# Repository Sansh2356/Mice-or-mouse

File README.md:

# Mouse PCB

Reverse-engineering the PCB of an optical mouse by tearing down wired single-chip and wireless dual-chip mice.
The circuit is traced using continuity measurements, then recreated in KiCad as a schematic, custom symbols/footprints, and a PCB layout.
Gerber files for the V1 board are generated and included in `gerbers/`.

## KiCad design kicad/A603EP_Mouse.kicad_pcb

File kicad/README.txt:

A603EP Mouse Clone - KiCad project
==================================
KiCad 7 format; opens in KiCad 7, 8 and 9 (newer versions offer to upgrade - click Yes).

Files
- A603EP_Mouse.kicad_pro        Project - open this
- A603EP_Mouse.kicad_sch        Schematic traced from board HYC-343-1
- A603EP_Mouse.kicad_pcb        PCB: outline, wheel slot, cable notch, chip/LED window, 8 holes,
                                and every part placed at its original position (not yet routed)
- A603EP_Mouse.kicad_sym / .pretty   Project symbols and footprints
- A603EP_PCB_fit_test.pdf       1:1 print to check the board against the original and the shell
- A603EP_Mouse_schematic.pdf    Printable schematic

How it was made
- Chip footprint: 1.778 mm pitch, 14.0 mm row spacing (confirmed by your paper test, option B).
- Everything else measured from your straight-down photo of the green side, using the chip pads
  as the ruler. Board comes out 38.9 x 66.4 mm (your ruler: 40 x 65). Accuracy about +-0.3 mm.
- KiCad's netlist and the PCB pad nets match the schematic exactly.

CHECKS - ALL DONE (19 Oct 2026)
- 1:1 fit test passed on the original board and in the shell.
- Encoder common = front outer leg; + = left leg for LED1, C1, D1-D4 ('+' marked on silkscreen); SW6 has 2 legs.
- Micro-switches: middle leg = common (pin 1), front = normally-open (pin 2), back = normally-closed (unused).

THEN ROUTE
- Route on one side (B.Cu) like the original if you want to etch at home, or use both sides
  if a fab makes it. Keep C2 close to U1 pins 10/11 and the USB tracks short.
- Run Inspect > Design Rules Checker. Order 1.6 mm thickness.

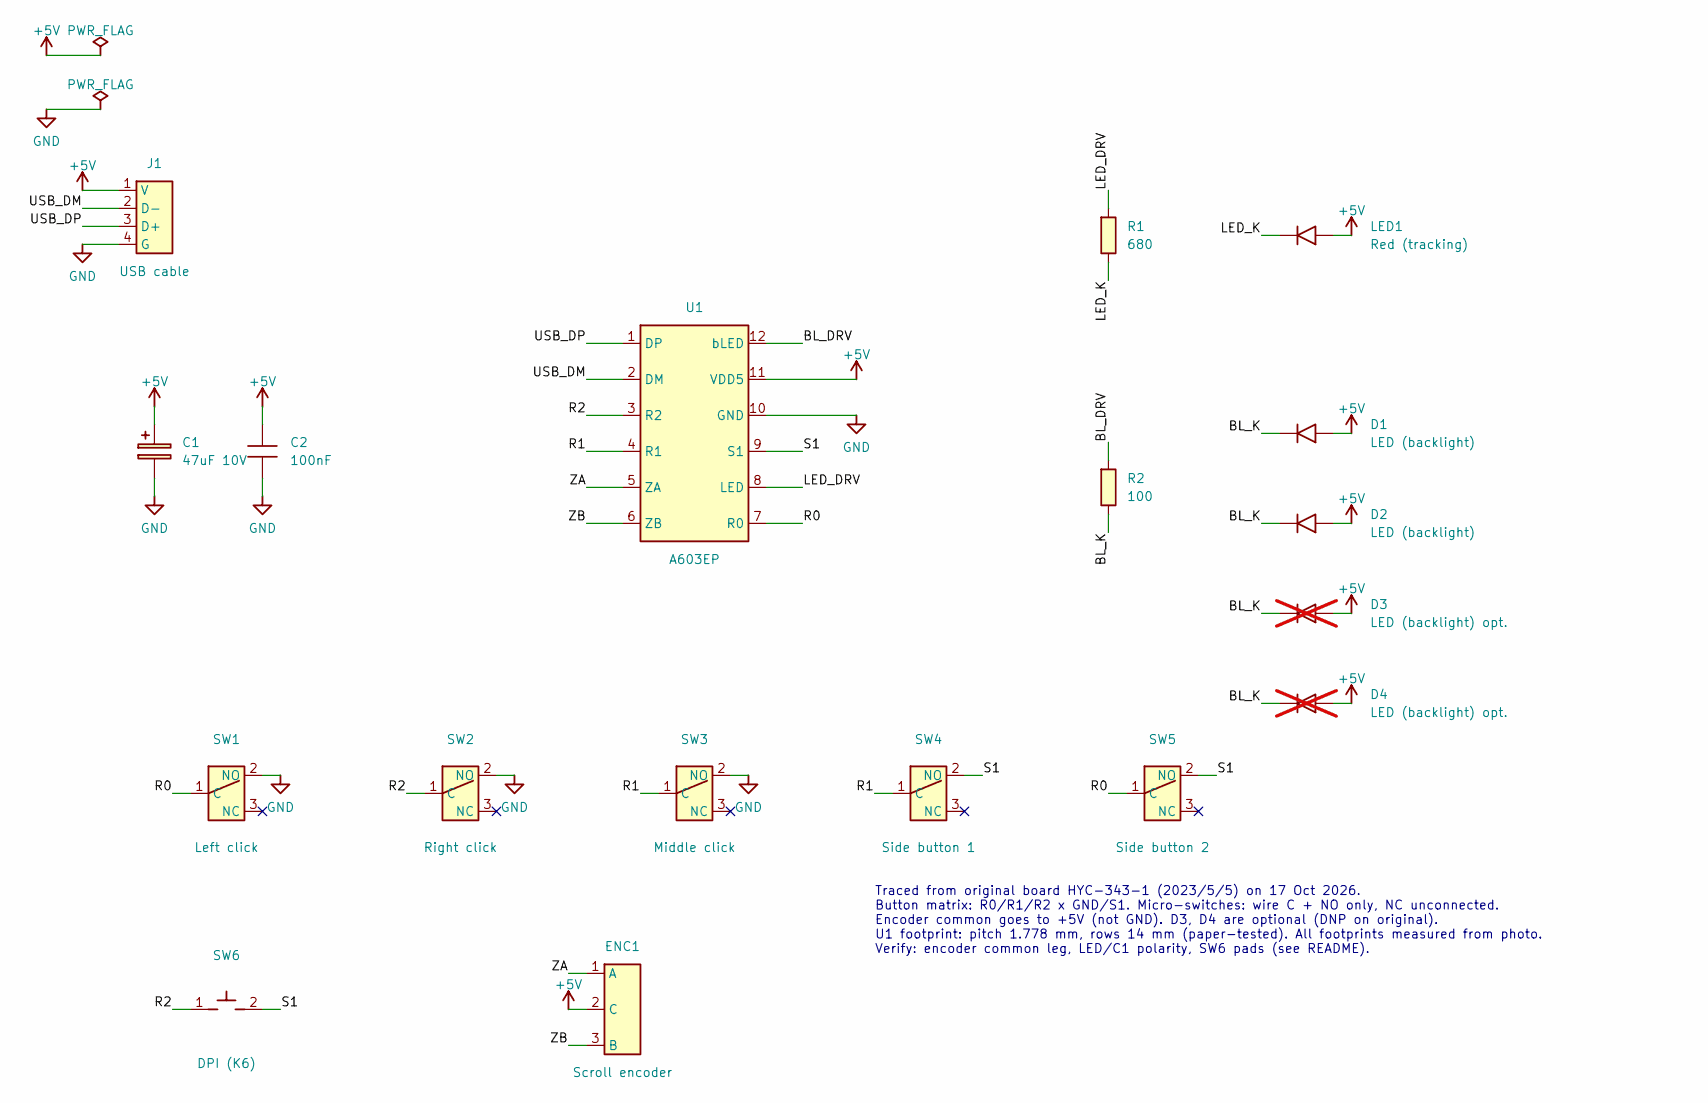
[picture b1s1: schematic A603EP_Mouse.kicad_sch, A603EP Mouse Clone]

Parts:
C1: 47uF 10V; C1_measured
C2: 100nF; C2_measured
D1: LED (backlight); D1_measured
D2: LED (backlight); D2_measured
D3: LED (backlight) opt.; D3_measured; not fitted
D4: LED (backlight) opt.; D4_measured; not fitted
ENC1: Scroll encoder; ENC1_measured
J1: USB cable; J1_measured
LED1: Red (tracking); LED1_measured
R1: 680; R1_measured
R2: 100; R2_measured
SW1: Left click; SW1_measured
SW2: Right click; SW2_measured
SW3: Middle click; SW3_measured
SW4: Side button 1; SW4_measured
SW5: Side button 2; SW5_measured
SW6: DPI (K6); SW6_measured
U1: A603EP; A603EP_DIP12

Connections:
+5V: C1.1, C2.1, D1.2 (A), D2.2 (A), D3.2 (A), D4.2 (A), ENC1.2 (C), J1.1 (V), LED1.2 (A), U1.11 (VDD5)
BL_DRV: R2.1, U1.12 (bLED)
BL_K: D1.1 (K), D2.1 (K), D3.1 (K), D4.1 (K), R2.2
GND: C1.2, C2.2, J1.4 (G), SW1.2 (NO), SW2.2 (NO), SW3.2 (NO), U1.10 (GND)
LED_DRV: R1.1, U1.8 (LED)
LED_K: LED1.1 (K), R1.2
R0: SW1.1 (C), SW5.1 (C), U1.7 (R0)
R1: SW3.1 (C), SW4.1 (C), U1.4 (R1)
R2: SW2.1 (C), SW6.1, U1.3 (R2)
S1: SW4.2 (NO), SW5.2 (NO), SW6.2, U1.9 (S1)
USB_DM: J1.2 (D-), U1.2 (DM)
USB_DP: J1.3 (D+), U1.1 (DP)
ZA: ENC1.1 (A), U1.5 (ZA)
ZB: ENC1.3 (B), U1.6 (ZB)

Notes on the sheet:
Traced from original board HYC-343-1 (2023/5/5) on 17 Oct 2026. Button matrix: R0/R1/R2 x GND/S1. Micro-switches: wire C + NO only, NC unconnected. Encoder common goes to +5V (not GND). D3, D4 are optional (DNP on original). U1 footprint: pitch 1.778 mm, rows 14 mm (paper-tested). All footprints me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

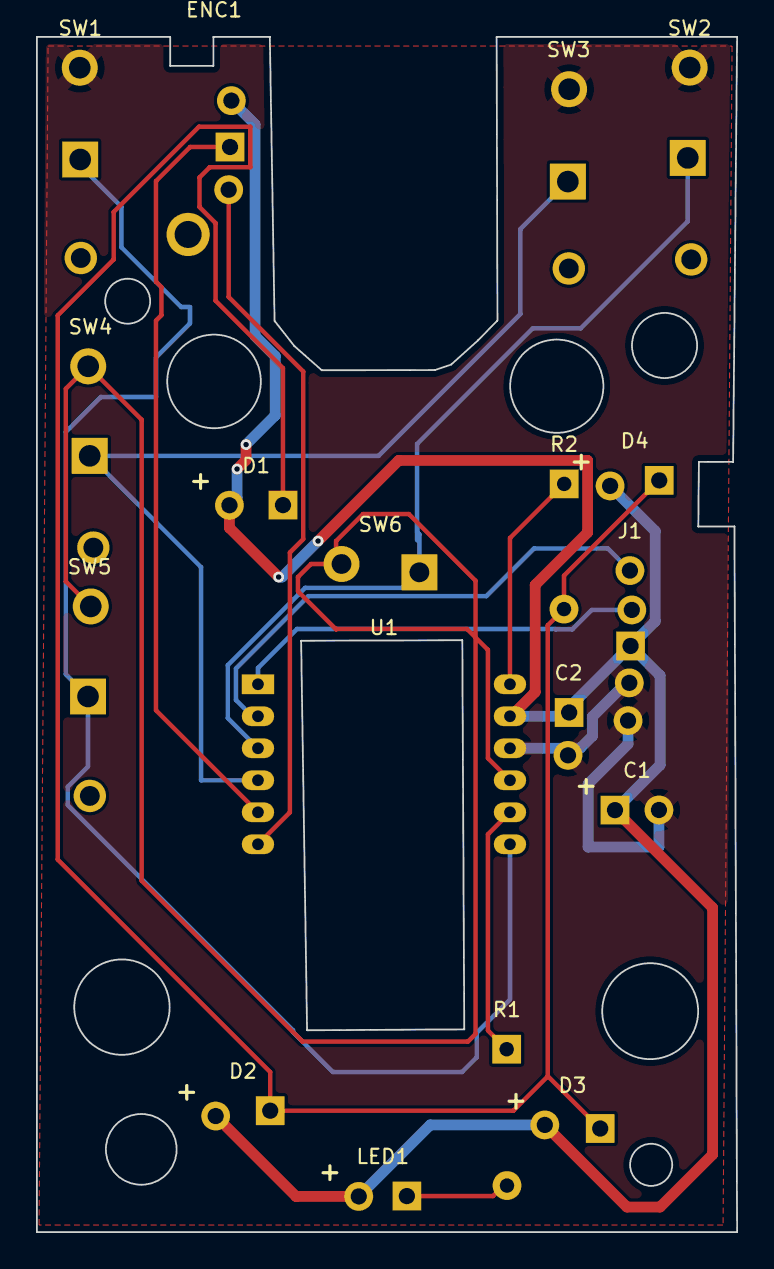
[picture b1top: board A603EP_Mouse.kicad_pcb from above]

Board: 2 copper layers, 38.9 x 66.4 mm, 18 parts (0 on the bottom side), 14 nets.
